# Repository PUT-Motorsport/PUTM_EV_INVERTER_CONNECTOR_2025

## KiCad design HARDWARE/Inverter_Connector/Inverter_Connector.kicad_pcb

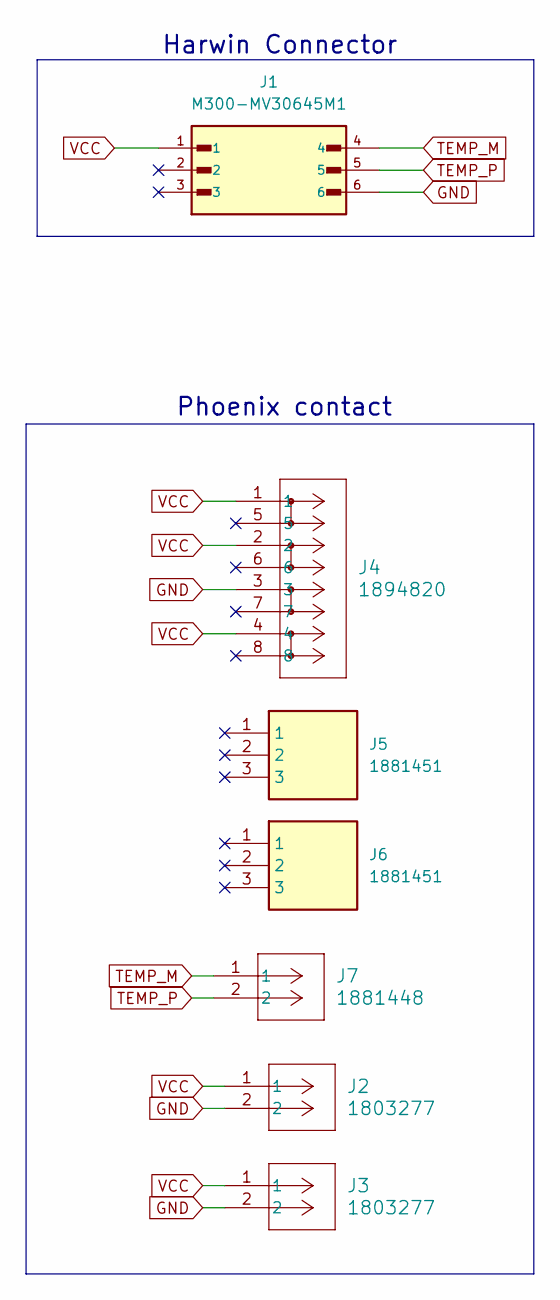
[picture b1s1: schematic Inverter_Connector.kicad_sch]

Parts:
J1: M300-MV30645M1; HARWIN_M300-MV30645M1; PARTREV 3
J2, J3: 1803277; CONN_1803277_PXC
J4: 1894820; CONN8_1894820_PXC
J5, J6: 1881451; Manufacturer_Part_Number 1881451; Mouser Part Number 651-1881451
J7: 1881448; CONN_1881448_PXC

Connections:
GND: J1.6, J2.2, J3.2, J4.3
TEMP_M: J1.4, J7.1
TEMP_P: J1.5, J7.2
VCC: J1.1, J2.1, J3.1, J4.1, J4.2, J4.4

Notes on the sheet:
Harwin Connector
Phoenix contact

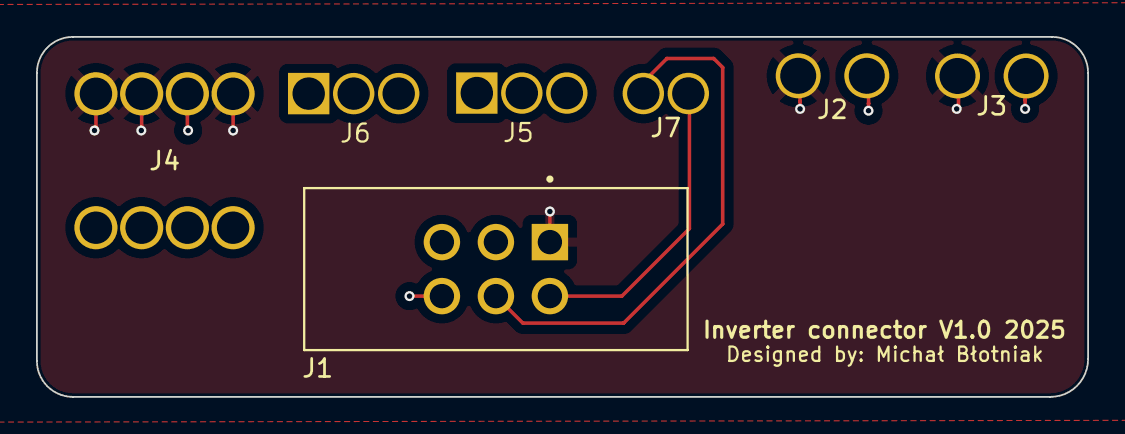
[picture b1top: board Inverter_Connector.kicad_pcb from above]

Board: 2 copper layers, 58.4 x 20.0 mm, 7 parts (0 on the bottom side), 4 nets.

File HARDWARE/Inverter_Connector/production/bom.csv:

Designator,Footprint,Quantity,Value,LCSC Part #
J1,HARWIN_M300-MV30645M1,1,M300-MV30645M1,
"J2, J3",CONN_1803277_PXC,2,1803277,
J4,CONN8_1894820_PXC,1,1894820,
"J5, J6",1881451,2,1881451,
J7,CONN_1881448_PXC,1,1881448,

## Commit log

2025-05-13 First version
2025-05-15 Corrected a typo
2025-05-15 Version 1.0
2025-05-15 After fix Version 1.1
2025-05-24 Production version
2025-05-24 Edit vias
2025-05-25 Production file
